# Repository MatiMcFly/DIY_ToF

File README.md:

# DIY ToF

Copyright (c) 2024-2025 Matthias Schär, Timon Burkard

This project is about creating a DIY (Do-It-Yourself) optical ToF (Time of Flight) distance measurement system.

It is a project work as part of the CAS (Certificate of Advanced Studies) in Sensors and Sensor Signal Conditioning, which is held at OST (Ostschweizer Fachhochschule) in Rapperswil CH.

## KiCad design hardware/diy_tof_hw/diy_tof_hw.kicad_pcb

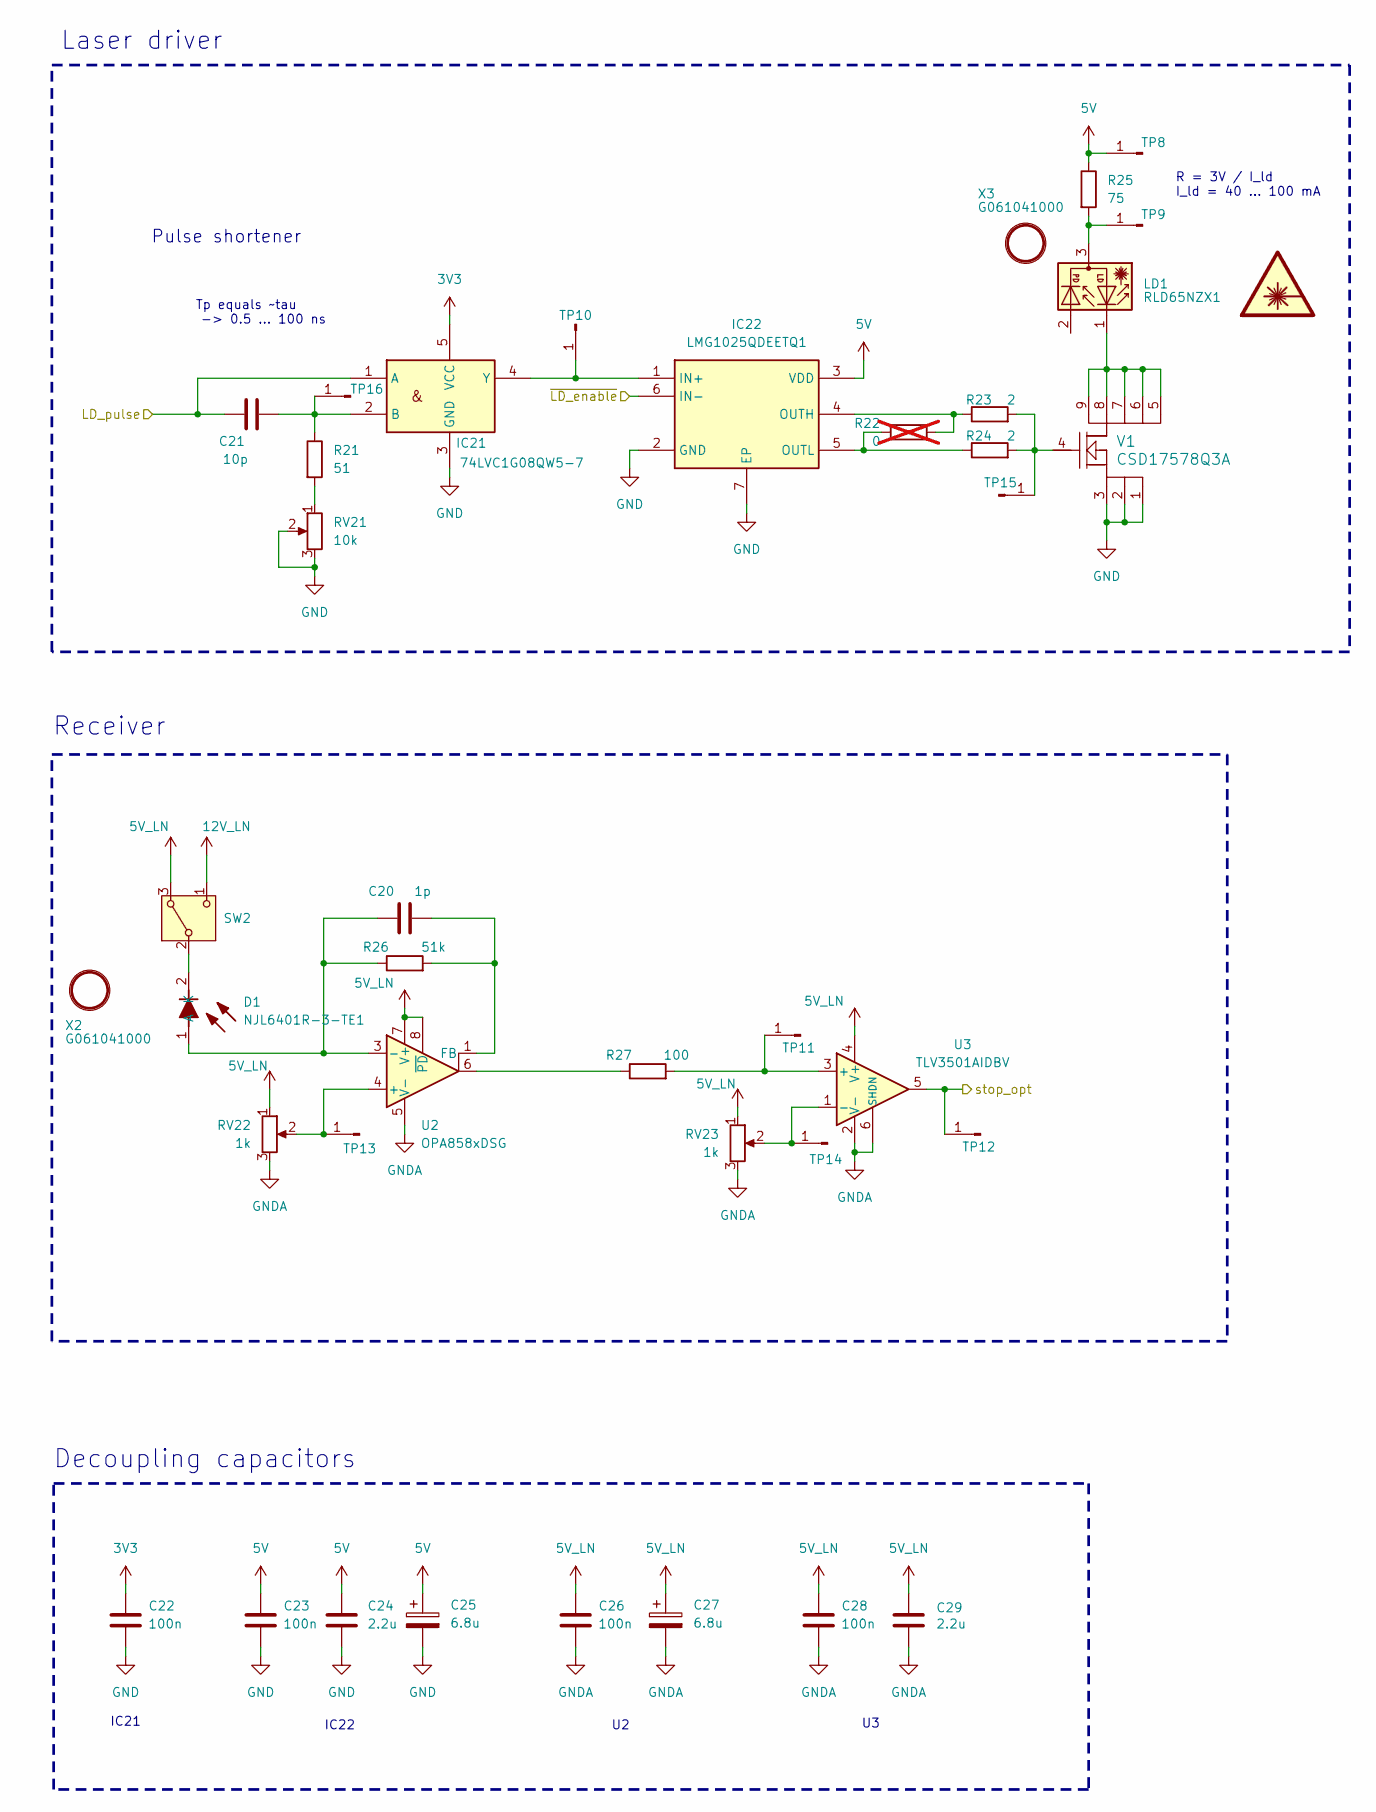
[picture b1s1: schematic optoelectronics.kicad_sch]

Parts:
C20: 1p; C_0402_1005Metric_Pad0.74x0.62mm_HandSolder
C21: 10p; C_0402_1005Metric_Pad0.74x0.62mm_HandSolder
C22, C23, C26, C28: 100n; C_0402_1005Metric_Pad0.74x0.62mm_HandSolder
C24, C29: 2.2u; C_0603_1608Metric_Pad1.08x0.95mm_HandSolder
C25, C27: 6.8u; CP_EIA-7343-43_Kemet-X_Pad2.25x2.55mm_HandSolder
D1: NJL6401R-3-TE1; NJL6401R3TE1; Mouser Part Number 513-NJL6401R-3-TE1
IC21: 74LVC1G08QW5-7; 74LVC1G08QW57; Mouser Part Number 621-74LVC1G08QW5-7
IC22: LMG1025QDEETQ1; SON65P200X200X80-7N; Mouser Part Number 595-LMG1025QDEETQ1
LD1: RLD65NZX1; RLD85PZJ400A
R21: 51; R_0402_1005Metric_Pad0.72x0.64mm_HandSolder
R22: 0; R_0402_1005Metric_Pad0.72x0.64mm_HandSolder; not fitted
R23, R24: 2; R_0402_1005Metric_Pad0.72x0.64mm_HandSolder
R25: 75; R_0603_1608Metric_Pad0.98x0.95mm_HandSolder
R26: 51k; R_0402_1005Metric_Pad0.72x0.64mm_HandSolder
R27: 100; R_0402_1005Metric_Pad0.72x0.64mm_HandSolder
RV21: 10k; Potentiometer_Bourns_3224W_Vertical
RV22, RV23: 1k; Potentiometer_Bourns_3224W_Vertical
SW2: SW_Nidec_CAS-120A1; Nidec_Copal_CAS-120A
TP8, TP9, TP10, TP11, TP12, TP13, TP14, TP15, TP16: Conn_01x01_Pin; PinHeader_1x01_P2.54mm_Vertical
U2: OPA858xDSG; WSON-8-1EP_2x2mm_P0.5mm_EP0.9x1.6mm
U3: TLV3501AIDBV; SOT-23-6
V1: CSD17578Q3A; DNH0008A
X2, X3: G061041000; Qioptiq_Mount

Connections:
3V3: C22.1, IC21.5 (VCC); also elsewhere on the board
5V: C23.1, C24.1, C25.1, IC22.3 (VDD), R25.1, TP8.1; also elsewhere on the board
5V_LN: C26.1, C27.1, C28.1, C29.1, RV22.1, RV23.1, SW2.3 (A), U2.7 (V+), U2.8 (~PD), U3.4 (V+); also elsewhere on the board
12V_LN: SW2.1 (C); also elsewhere on the board
/Optoelectronics/LD_pulse: C21.1, IC21.1 (A); also elsewhere on the board
/Optoelectronics/stop_opt: TP12.1, U3.5; also elsewhere on the board
/Optoelectronics/~LD_enable: IC22.6 (IN-); also elsewhere on the board
GND: C22.2, C23.2, C24.2, C25.2, IC21.3 (GND), IC22.2 (GND), IC22.7 (EP), RV21.2, RV21.3, V1.1, V1.2, V1.3; also elsewhere on the board
GNDA: C26.2, C27.2, C28.2, C29.2, RV22.3, RV23.3, U2.5 (V-), U2.9 (V-), U3.2 (V-), U3.6 (SHDN); also elsewhere on the board
unnamed: C20.1, D1.1 (A), R26.1, U2.3 (-)
unnamed: D1.2 (K), SW2.2 (B)
unnamed: C21.2, IC21.2 (B), R21.1, TP16.1
unnamed: IC21.4 (Y), IC22.1 (IN+), TP10.1
unnamed: IC22.4 (OUTH), R22.2, R23.1
unnamed: IC22.5 (OUTL), R22.1, R24.1
unnamed: LD1.1, V1.5, V1.6, V1.7, V1.8, V1.9
unnamed: R21.2, RV21.1
unnamed: R27.1, U2.6
unnamed: LD1.3, R25.2, TP9.1
unnamed: R27.2, TP11.1, U3.3 (+)
unnamed: RV22.2, TP13.1, U2.4 (+)
unnamed: RV23.2, TP14.1, U3.1 (-)
unnamed: R23.2, R24.2, TP15.1, V1.4
unnamed: C20.2, R26.2, U2.1 (FB)

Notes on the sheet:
Decoupling capacitors
IC22
Laser driver
R = 3V / I_ld I_ld = 40 ... 100 mA
Tp equals ~tau -> 0.5 ... 100 ns
IC21
Receiver
Pulse shortener

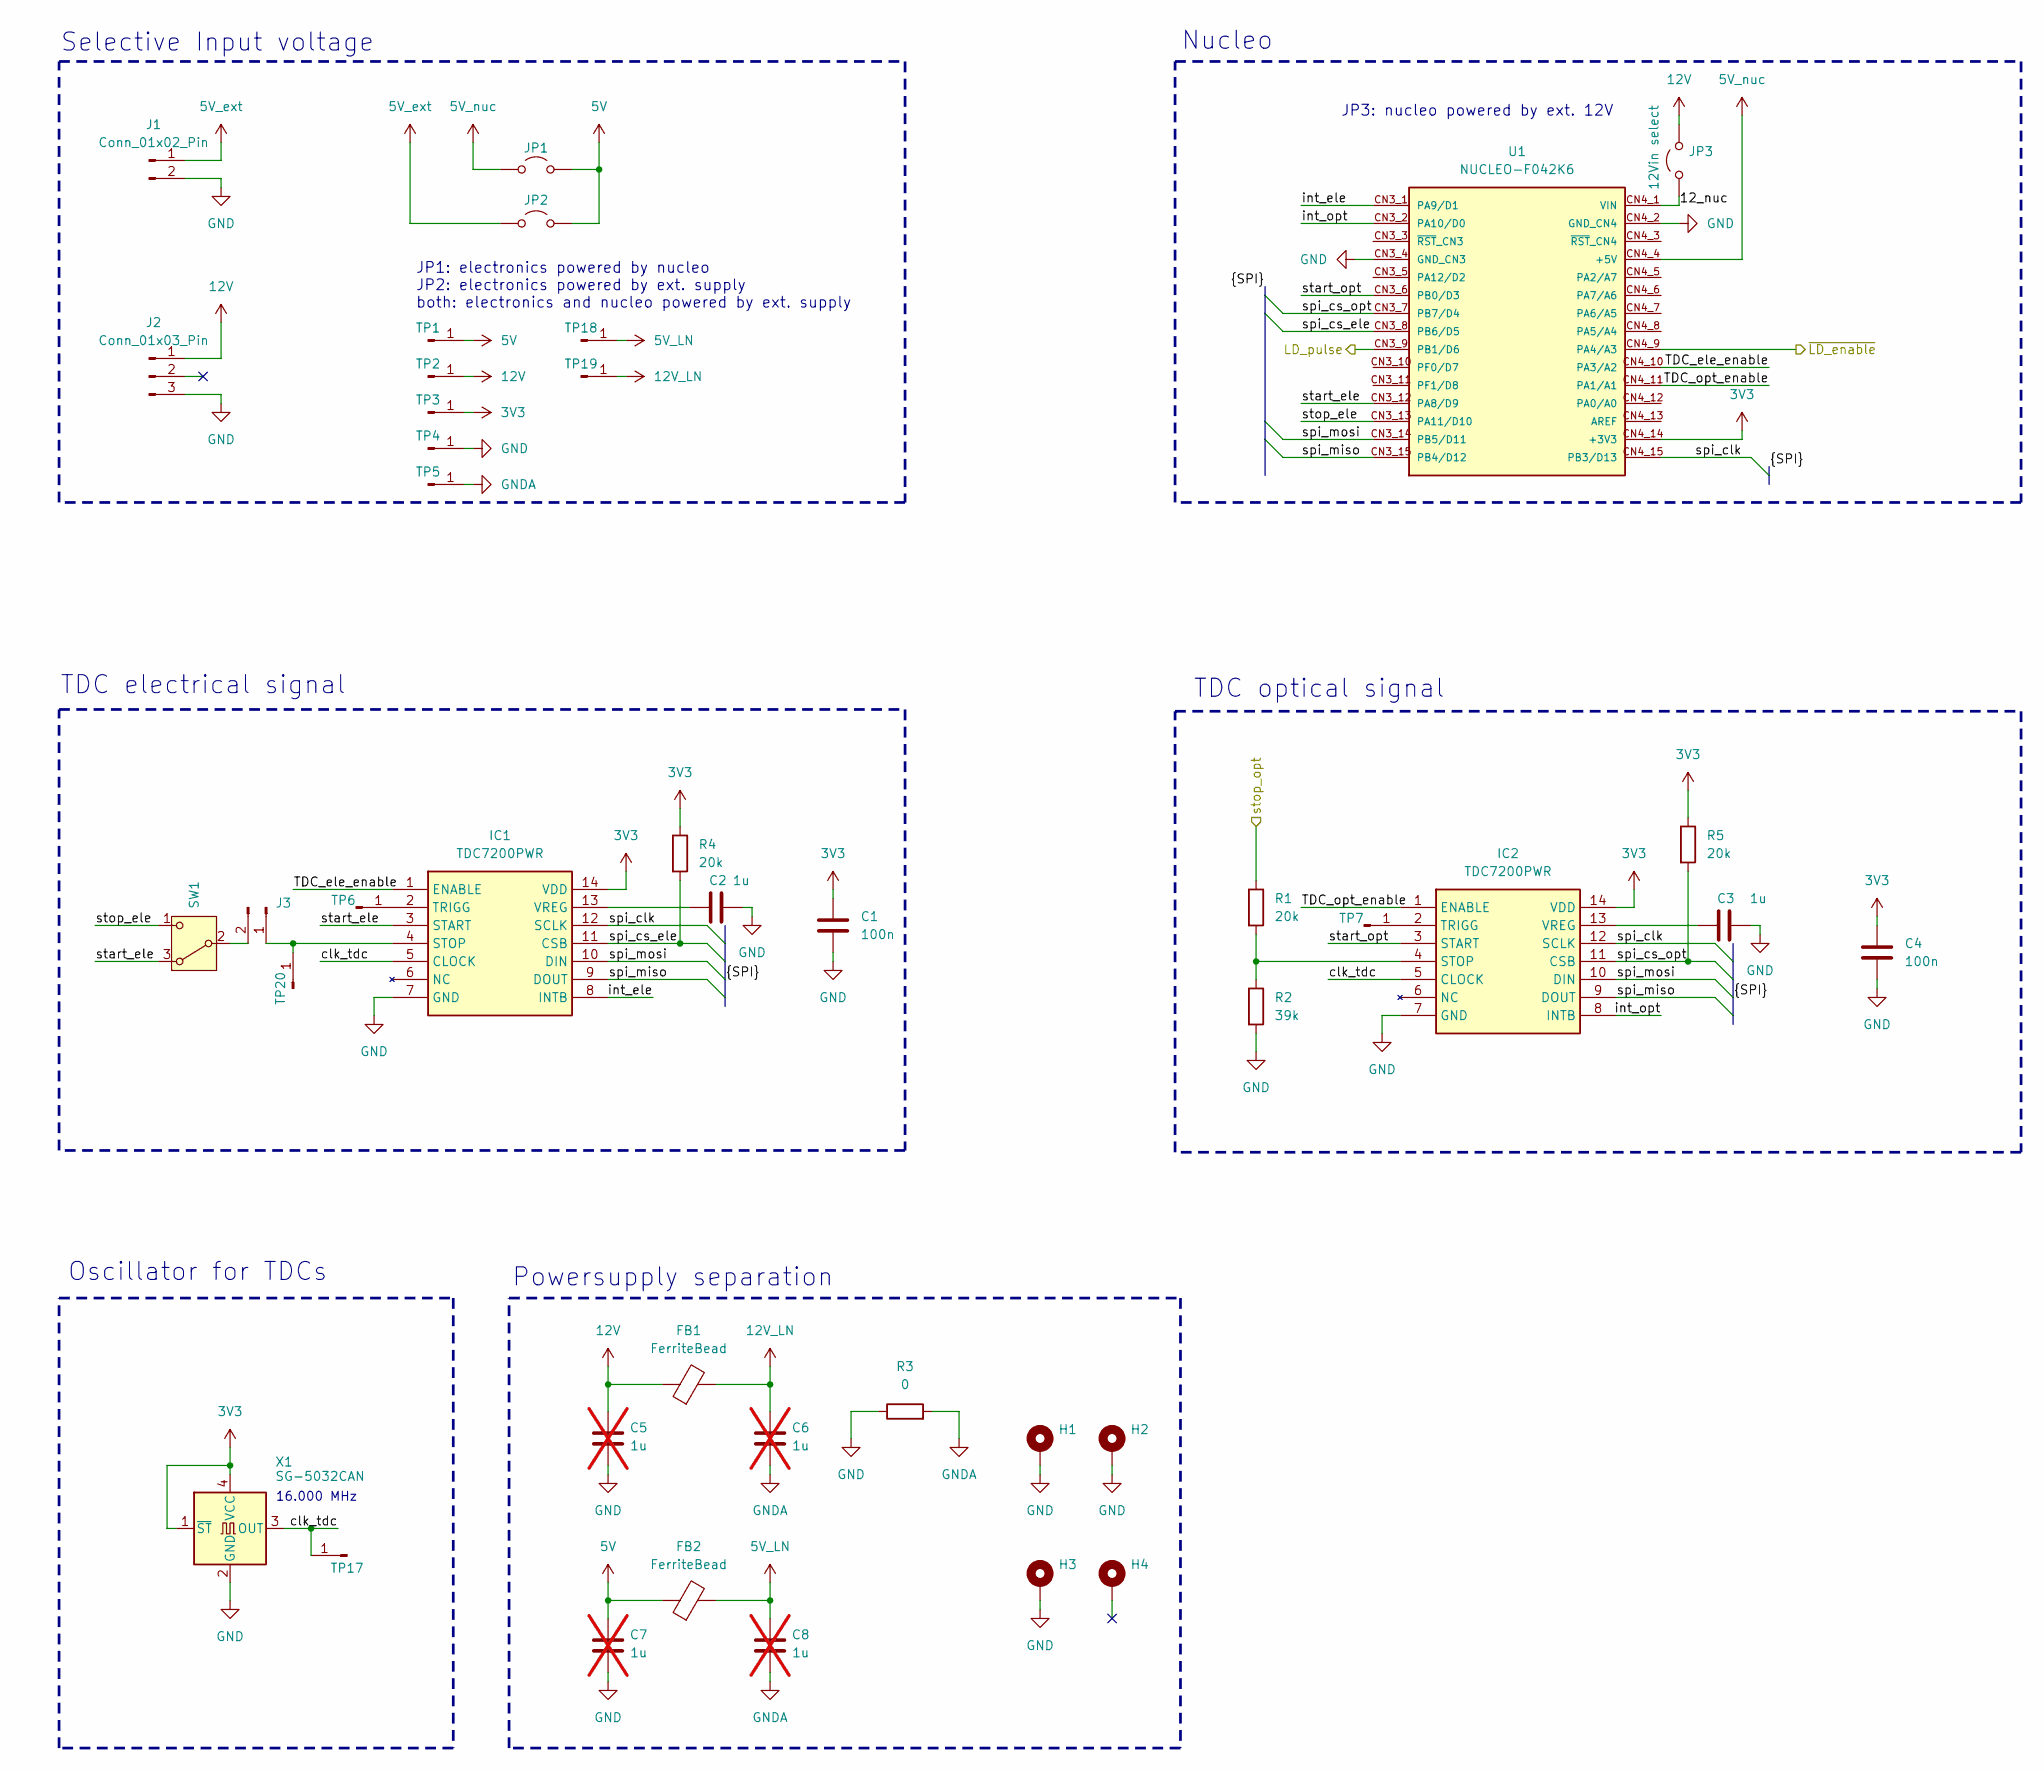
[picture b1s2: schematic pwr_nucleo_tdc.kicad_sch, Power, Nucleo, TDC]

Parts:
C1, C4: 100n; C_0402_1005Metric_Pad0.74x0.62mm_HandSolder
C2, C3: 1u; C_0402_1005Metric_Pad0.74x0.62mm_HandSolder
C5, C6, C7, C8: 1u; C_0402_1005Metric_Pad0.74x0.62mm_HandSolder; not fitted
FB1, FB2: FerriteBead; L_0402_1005Metric_Pad0.77x0.64mm_HandSolder
H1, H2, H3, H4: MountingHole_Pad; MountingHole_3.2mm_M3_DIN965_Pad_TopBottom
IC1, IC2: TDC7200PWR; SOP65P640X120-14N; Mouser Part Number 595-TDC7200PWR
J1, J3: Conn_01x02_Pin; Molex_KK-254_AE-6410-02A_1x02_P2.54mm_Vertical
J2: Conn_01x03_Pin; Molex_SL_171971-0003_1x03_P2.54mm_Vertical
JP1, JP2: Jumper_2_Open; TestPoint_2Pads_Pitch2.54mm_Drill0.8mm
JP3: 12Vin select; TestPoint_2Pads_Pitch2.54mm_Drill0.8mm
R1, R4, R5: 20k; R_0402_1005Metric_Pad0.72x0.64mm_HandSolder
R2: 39k; R_0402_1005Metric_Pad0.72x0.64mm_HandSolder
R3: 0; R_0402_1005Metric_Pad0.72x0.64mm_HandSolder
SW1: SW_Nidec_CAS-120A1; Nidec_Copal_CAS-120A
TP1, TP2, TP3, TP4, TP5, TP6, TP7, TP17, TP18, TP19, TP20: Conn_01x01_Pin; PinHeader_1x01_P2.54mm_Vertical
U1: NUCLEO-F042K6; MODULE_NUCLEO-F042K6; PARTREV 8
X1: SG-5032CAN; Oscillator_SMD_SeikoEpson_SG8002LB-4Pin_5.0x3.2mm_HandSolde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

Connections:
3V3: C1.1, C4.1, IC1.14 (VDD), IC2.14 (VDD), R4.1, R5.1, TP3.1, U1.CN4_14 (+3V3), X1.1 (~ST), X1.4 (VCC); also elsewhere on the board
5V: C7.2, FB2.1, JP1.2 (B), JP2.2 (B), TP1.1; also elsewhere on the board
5V_LN: C8.2, FB2.2, TP18.1; also elsewhere on the board
5V_ext: J1.1, JP2.1 (A)
5V_nuc: JP1.1 (A), U1.CN4_4 (+5V)
12V: C5.2, FB1.1, J2.1, JP3.2 (B), TP2.1
12V_LN: C6.2, FB1.2, TP19.1; also elsewhere on the board
/Optoelectronics/LD_pulse: U1.CN3_9 (PB1/D6); also elsewhere on the board
/Optoelectronics/stop_opt: R1.1; also elsewhere on the board
/Optoelectronics/~LD_enable: U1.CN4_9 (PA4/A3); also elsewhere on the board
/Power_Nucleo_TDC/12_nuc: JP3.1 (A), U1.CN4_1 (VIN)
/Power_Nucleo_TDC/TDC_ele_enable: IC1.1 (ENABLE), U1.CN4_10 (PA3/A2)
/Power_Nucleo_TDC/TDC_opt_enable: IC2.1 (ENABLE), U1.CN4_11 (PA1/A1)
/Power_Nucleo_TDC/clk_tdc: IC1.5 (CLOCK), IC2.5 (CLOCK), TP17.1, X1.3 (OUT)
/Power_Nucleo_TDC/int_ele: IC1.8 (INTB), U1.CN3_1 (PA9/D1)
/Power_Nucleo_TDC/int_opt: IC2.8 (INTB), U1.CN3_2 (PA10/D0)
/Power_Nucleo_TDC/spi_clk: IC1.12 (SCLK), IC2.12 (SCLK), U1.CN4_15 (PB3/D13)
/Power_Nucleo_TDC/spi_cs_ele: IC1.11 (CSB), R4.2, U1.CN3_8 (PB6/D5)
/Power_Nucleo_TDC/spi_cs_opt: IC2.11 (CSB), R5.2, U1.CN3_7 (PB7/D4)
/Power_Nucleo_TDC/spi_miso: IC1.9 (DOUT), IC2.9 (DOUT), U1.CN3_15 (PB4/D12)
/Power_Nucleo_TDC/spi_mosi: IC1.10 (DIN), IC2.10 (DIN), U1.CN3_14 (PB5/D11)
/Power_Nucleo_TDC/start_ele: IC1.3 (START), SW1.3 (A), U1.CN3_12 (PA8/D9)
/Power_Nucleo_TDC/start_opt: IC2.3 (START), U1.CN3_6 (PB0/D3)
/Power_Nucleo_TDC/stop_ele: SW1.1 (C), U1.CN3_13 (PA11/D10)
GND: C1.2, C2.2, C3.2, C4.2, C5.1, C7.1, H1.1, H2.1, H3.1, IC1.7 (GND), IC2.7 (GND), J1.2, J2.3, R2.2, R3.1, TP4.1, U1.CN3_4 (GND_CN3), U1.CN4_2 (GND_CN4), X1.2 (GND); also elsewhere on the board
GNDA: C6.1, C8.1, R3.2, TP5.1; also elsewhere on the board
unnamed: IC1.4 (STOP), J3.1, TP20.1
unnamed: IC1.2 (TRIGG), TP6.1
unnamed: C2.1, IC1.13 (VREG)
unnamed: IC2.4 (STOP), R1.2, R2.1
unnamed: IC2.2 (TRIGG), TP7.1
unnamed: C3.1, IC2.13 (VREG)
unnamed: J3.2, SW1.2 (B)

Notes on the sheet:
Powersupply separation
Oscillator for TDCs
Nucleo
JP1: electronics powered by nucleo JP2: electronics powered by ext. supply both: electronics and nucleo powered by ext. supply
TDC optical signal
Selective Input voltage
16.000 MHz
JP3: nucleo powered by ext. 12V
TDC electrical signal

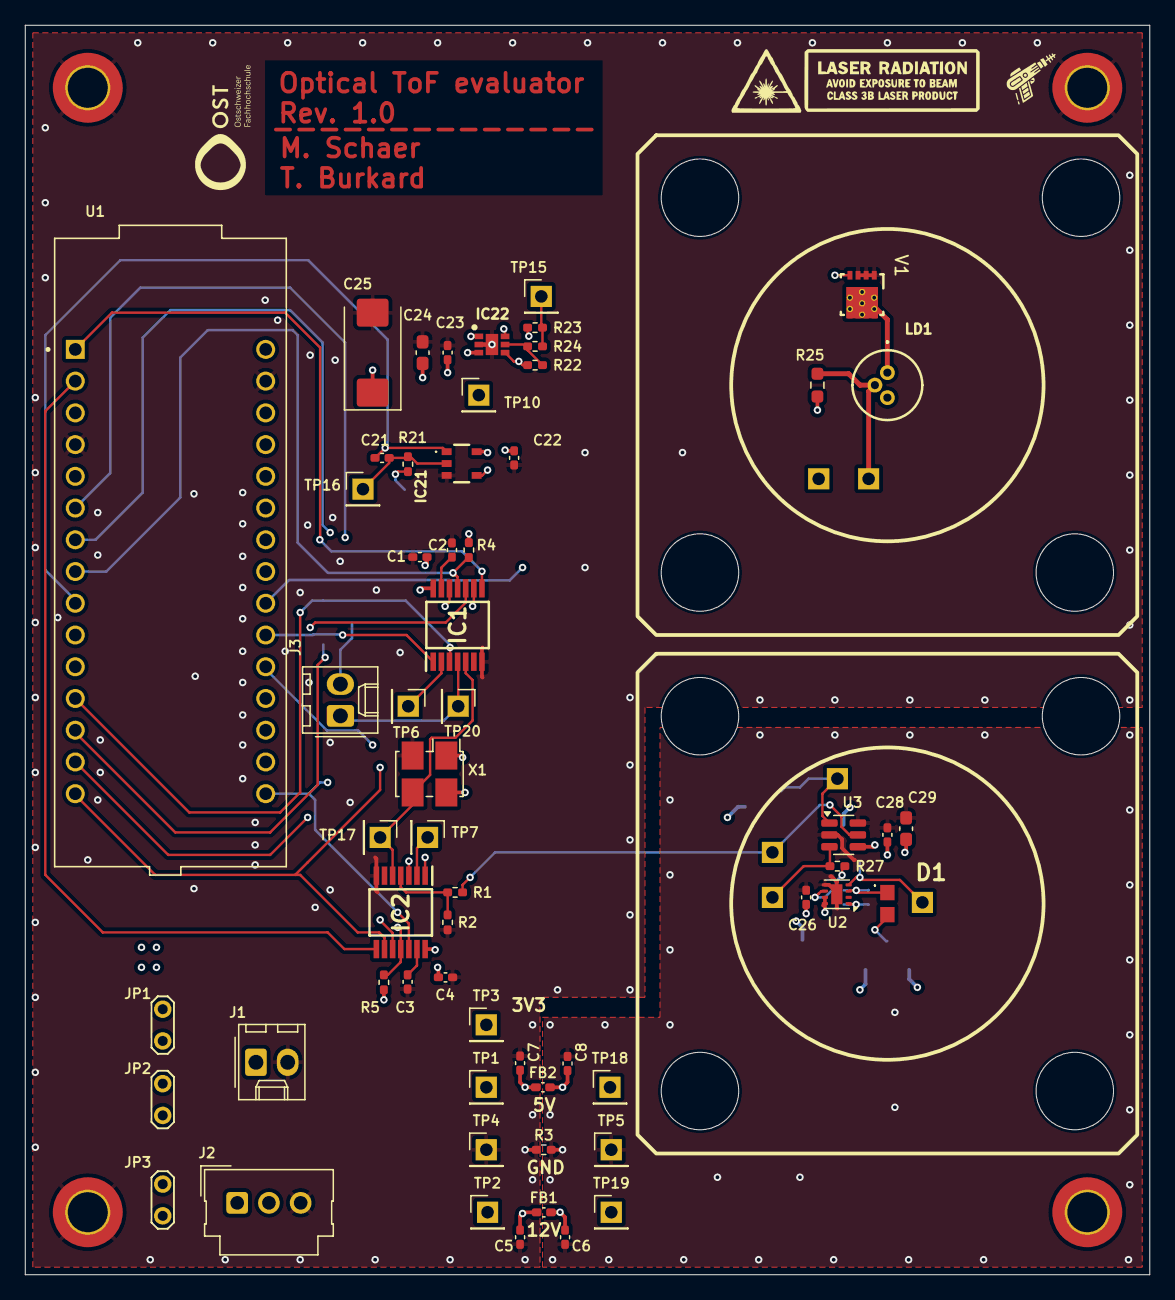
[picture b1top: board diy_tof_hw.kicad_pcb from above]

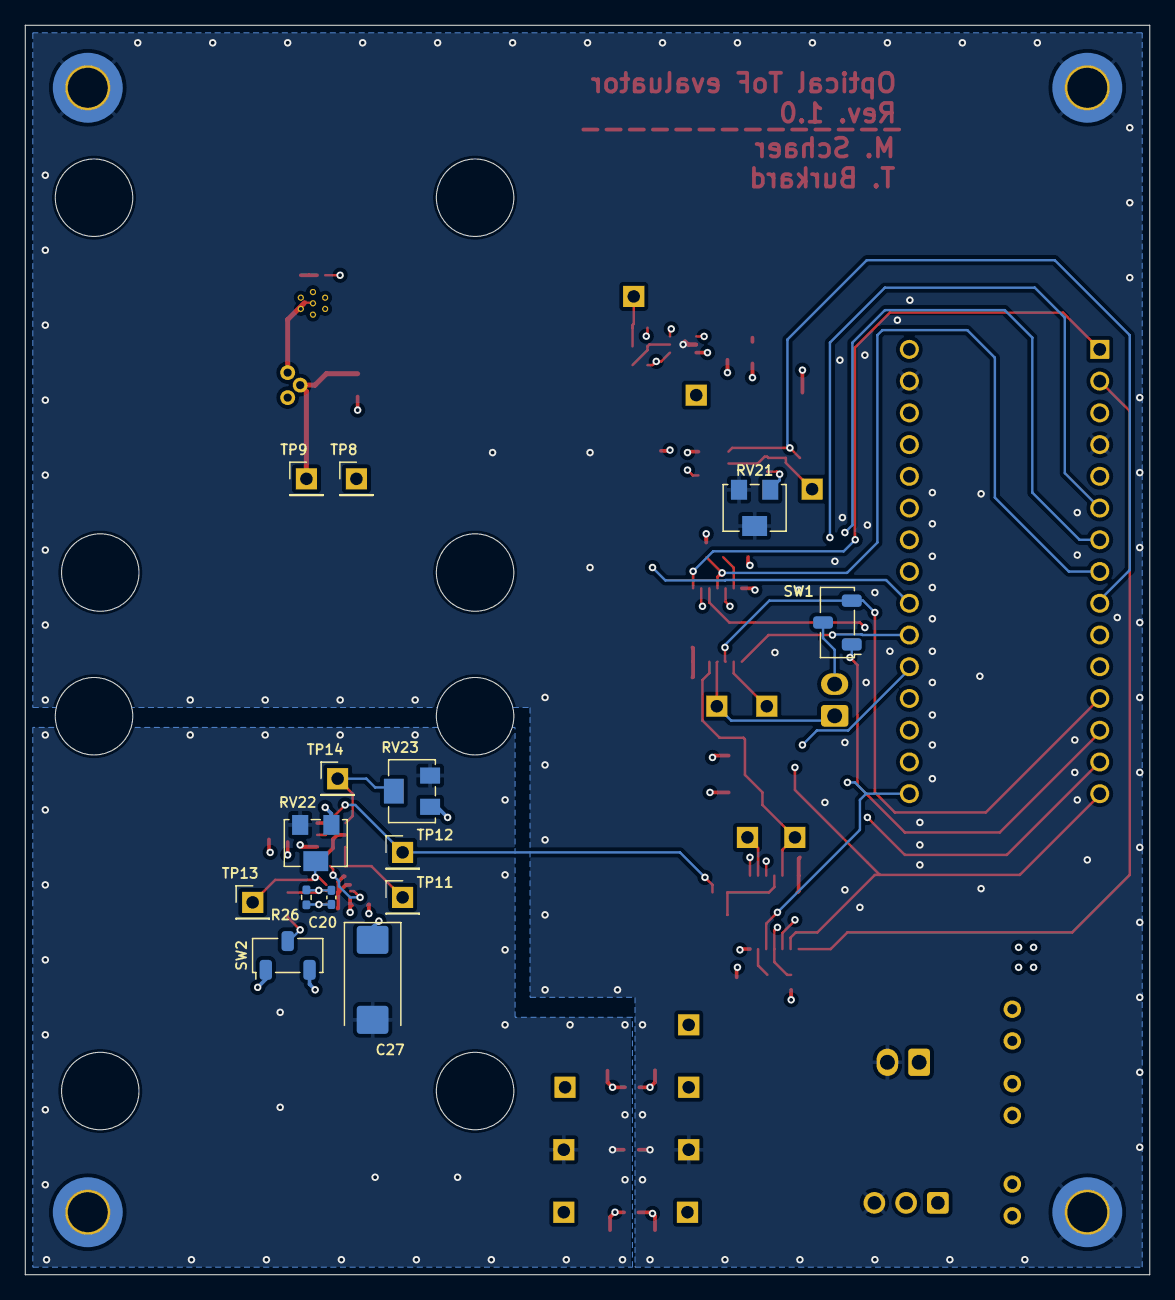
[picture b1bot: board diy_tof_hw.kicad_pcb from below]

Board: 4 copper layers, 90.0 x 100.0 mm, 80 parts (14 on the bottom side), 48 nets.

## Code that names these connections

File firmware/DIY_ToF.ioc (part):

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Mcu.Name=STM32F042K(4-6)Tx
Mcu.Package=LQFP32
Mcu.UserName=STM32F042K6Tx
PA1.GPIOParameters=GPIO_Label
PA1.GPIO_Label=TDC_OPT_ENABLE
PA1.Signal=GPIO_Output
PA10.GPIOParameters=GPIO_Label
PA10.GPIO_Label=INT_OPT
PA10.Signal=GPXTI10
PA11.GPIOParameters=GPIO_Label
PA11.GPIO_Label=STOP_ELE
PA11.Signal=S_TIM1_CH4
PA13.GPIOParameters=GPIO_Label
PA13.GPIO_Label=SWDIO
PA13.Mode=Serial_Wire
PA13.Signal=SYS_SWDIO
PA14.GPIOParameters=GPIO_Label
PA14.GPIO_Label=SWCLK
PA14.Mode=Serial_Wire
PA14.Signal=SYS_SWCLK
PA15.GPIOParameters=GPIO_Label
PA15.GPIO_Label=VCP_RX
PA15.Mode=Asynchronous
PA15.Signal=USART2_RX
PA2.GPIOParameters=GPIO_Label
PA2.GPIO_Label=VCP_TX
PA2.Mode=Asynchronous
PA2.Signal=USART2_TX
PA3.GPIOParameters=GPIO_Label
PA3.GPIO_Label=TDC_ELE_ENABLE
PA3.Signal=GPIO_Output
PA4.GPIOParameters=GPIO_Label
PA4.GPIO_Label=LD_ENABLE
PA4.Signal=GPIO_Output
PA8.GPIOParameters=GPIO_Label
PA8.GPIO_Label=START_ELE
PA8.Signal=S_TIM1_CH1
PA9.GPIOParameters=GPIO_Label
PA9.GPIO_Label=INT_ELE
PA9.Signal=GPXTI9
PB0.GPIOParameters=GPIO_Label
PB0.GPIO_Label=START_OPT
PB0.Signal=S_TIM3_CH3
PB1.GPIOParameters=GPIO_Label
PB1.GPIO_Label=LD_PULSE
PB1.Signal=S_TIM3_CH4
PB3.GPIOParameters=GPIO_Label
PB3.GPIO_Label=SPI_CLK
PB3.Mode=Full_Duplex_Master
PB3.Signal=SPI1_SCK
PB4.GPIOParameters=GPIO_Label
PB4.GPIO_Label=SPI_MISO
PB4.Mode=Full_Duplex_Master
PB4.Signal=SPI1_MISO
PB5.GPIOParameters=GPIO_Label
PB5.GPIO_Label=SPI_MOSI
PB5.Mode=Full_Duplex_Master
PB5.Signal=SPI1_MOSI
PB6.GPIOParameters=GPIO_Label
PB6.GPIO_Label=SPI_CS_ELE
PB6.Signal=GPIO_Output
PB7.GPIOParameters=GPIO_Label
PB7.GPIO_Label=SPI_CS_OPT
PB7.Signal=GPIO_Output
PF0-OSC_IN.GPIOParameters=GPIO_Label
PF0-OSC_IN.GPIO_Label=MCO
PF0-OSC_IN.Mode=HSE-External-Clock-Source
PF0-OSC_IN.Signal=RCC_OSC_IN
RCC.SYSCLKFreq_VALUE=48000000
RCC.SYSCLKSource=RCC_SYSCLKSOURCE_HSI48
board=NUCLEO-F042K6
boardIOC=true

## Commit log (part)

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2024-12-18 [general] initial commit
2024-12-18 [firmware] initial commit based on default MX board configuration
2024-12-18 [firmware] added GPIO configuration
    GPIO configuration for the following pins has been added:
    - SPI MISO
    - SPI MOSI
    - SPI CLK
    - SPI CS ELE
    - SPI CS OPT
2024-12-18 [docs] initial latex setup incl. some examples
2024-12-19 [hardware] initial commit containing KiCad project (schematics, layout and example library)
2024-12-20 [firmware/ci] trigger github action only for changes in firmware/ directory
    Github action only builds the STM32 FW project, no need to trigger it for changes in other directories.
2024-12-21 [hardware] added new templates for schematic files
2024-12-22 [hardware] drawn initial version of the power / nucleo sheet
2024-12-22 [firmware] modified IO signals - removed signal "PEAK_OPT" - added signals "LD_ENABLE", "LD_PULSE" and "TDC_ENABLE"
2024-12-22 [hardware] added schematics and library components for the laser driver as well as TIA circuit
2024-12-24 [hardware] cherry picked changes from review
    [hardware] add description text for JP3
    (cherry picked from commit 44d5712227eb7a57076d25d490ffb1ca2a138412)
    [hardware] use relative path for schematics template
    (cherry picked from commit 5e7c5f0f6d85de52cfba936180bf5f2080214473)
    [hardware] use explicit path to STEP files for U1, IC1, IC2, IC21, IC22
    (cherry picked from commit 2ea5c7e3506b8eddbb4935cb7e42b338c20b0635)
2024-12-24 [hardware, firmware] various review findings - added new signals TDC_opt/ele_enable - fixed placement and appearance of the optics mount - added switch for stop signal of the electrical TDC - replace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
2024-12-24 [hardware] renamed sheet "pwr_nucleo" to "pwr_nucleo_tdc"
2024-12-24 [hardware] added VCSEL, photodiode and some pcb graphics to the project
2024-12-24 [firmware] regenerated code due to previous IOC changes
    (cherry picked from commit fda93d0817f41cd3d09d576f384de487f9e32325)
2024-12-24 [hardware] updating 3D models again
2024-12-25 [hardware] added missing TP20
2024-12-25 [docs] initial chapter structure
2024-12-25 [hardware/minor] added title for optoelectronics schematic page
2024-12-25 [docs] remove examples from template
2024-12-25 [docs] added 3D views
2024-12-25 [docs] added 2nd professor
2024-12-25 [docs] added schematic drawings
2024-12-25 [docs] added calculations for photo current
2024-12-25 [docs] regenerated PDF due to latest changes
2024-12-26 [docs] move numbering of Formelverzeichnis a bit to the right
    To be harmonized with other Verzeichnisse
2024-12-26 [docs] added more references of components
2024-12-26 [docs] added some more text around calculations and schematics
2024-12-27 [hardware] changed footprint of R25 to 0603, updated some ICs footprint models in order to comply with e.g. via hole size constraints
2024-12-27 [hardware] initial version of the PCB layout
2024-12-27 [hardware] placed all components, some minor renaming (got rid of the "+" in front of all source-labels)
2024-12-27 [hardware] enlarged planes so that the PCB won't be produced with asymmetric copper planes - also added gerber output job
2024-12-27 [hardware] minor plane adjustments, removed a connection which is done via plane
2024-12-27 [hardware] review findings - moved powerplanes to layer In1 - added ground planes on all other layers - rerouting of signals around the nucleo board, leaving enough space for ground fills
2024-12-27 [docs] added PCB layout plots
2024-12-27 [docs] updated BOM based on recent changes in KiCAD
2024-12-27 [hardware/minor] add value for optic mountings
2025-01-08 [firmware/tdc] added initial version of TDC driver
2025-01-08 [firmware/tdc] added more register information
2025-01-08 [firmware/test] added quick example to test TDC driver implementation
2025-01-11 [firmware/tdc] add delay after CS high
    Just as an extra safety measure to ensure that we wait long enough
    after CS high until we start a measurement.
2025-01-11 [firmware/tdc] added `TDC_start()` and `TDC_read_result()` functions
2025-01-12 [utilities] added python script for stats calculation and plots
2025-01-12 [docs] added TDC driver and python script to Anhang
2025-01-12 [docs/minor] implemented max. line length of 120
    Not all editors support line wrapping. And this improves `git diff`.
2025-01-12 [utilities] added python script for stats calculation and plots for multiple measurements
2025-01-12 [docs] added python script multi to Anhang
2025-01-12 [docs] added chapter "Elektrische Messungen / Mode 1 vs. Mode 2"
2025-01-12 [docs] added chapter "Elektrische Messungen / Unterschiedliche Kabellängen"
2025-01-12 [docs] changed formulation about SW1 and J3 measurement settings
2025-01-15 [docs] added new section "konzept" since we need to explain various things like why we decided to use 2 TDCs; added some explanations for the nucleo schematics
2025-01-15 [docs] - added calculation for "lens gain" - added content to chapter "konzept" - added whole schematics to appendix - moved BoM to appendix - regenerated schematic with changes from v1.0
2025-01-15 [docs] added some more text to schematics
2025-01-15 [docs] rebuilt documentation.pdf after rebase and fixed another review finding
2025-01-15 [docs] no need to use sub-ps resolution
    THe TDC has 55~ps resolution. No need to use sub-ps resolution in docs.
2025-01-15 [docs] added chapter "Elektrische Messungen / Unterschiedliche Clock-Konfigurationen"
2025-01-15 [docs] applied feedback from review
2025-01-15 [docs/minor] harmonization of references to Anhang
    We agreed to call it `Anhang~\ref{...}` instead of `Anhang Kapitel~\ref{...}`
2025-01-15 [docs/minor] harmonization: all references to schematic designators should habe `\lstinline|...|`
2025-01-15 [docs] fixed typos
2025-01-15 [docs] added some more details about SW1
2025-01-15 [docs/minor] don't use `\acrshort{tdc}` as part of the component TDC7200
2025-01-15 [docs] restructuring: separate TEX files for each chapter
2025-01-16 [docs] added photos of demonstrator and lens
2025-01-16 [docs] added chapter "Simulationen / Laser Treiber"
2025-01-16 [docs] added chapter "Simulationen / Transimpedanzverstärker"
2025-01-16 [docs] structure: changed order of "Umsetzung" und "Simulationen"
    Makes more sense for "Simulationen" to come first. As we did the simulations
    first and only after we started the implementation (schematic, layout, ...)
2025-01-16 [docs] added some more equations for the optical path
2025-01-16 [docs] added text and a small diagram to the theory chapter
2025-01-16 [docs] added some basic text and a circuit diagram regarding the transimpedance amplifier
2025-01-17 [docs] review findings - some more correctures in various formulas - recalculated output power of the LD in both scenarios - better formulations + some typos fixed - better TIA schematics -> thanks T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
2025-01-17 [firmware] setup TIM1 channel 1 and 4 (start/stop ele) in order to do future measurements with less jitter
2025-01-17 [firmware] changed to 48 MHz clock by using HSI48 clock source
2025-01-17 [firmware] changed timer mode to one pulse mode - timer runs for 1.4ms, therefore the measurement loop delay was shortened to 2 ms
2025-01-17 [firmware] IO configuration for TIM3 in order to measure TDC optical the same way as the electrical one - start_opt and ld_pulse are now generated with TIM3
2025-01-18 [docs] rearrangements and picture updates - rearranged chapter "Umsetzung" into correct chronological order - applied the same changes to the appendix - moved all photos / 3D views / placement and la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
2025-01-18 [docs] sub sub chapters "Layout" and "3D View" - also modified text at beginning of chapter - added context for trimmers in the TIA schematics section
2025-01-18 [docs] recalculated optical power and light current more accurately, fixed a reference in the concept chapter - some formulations changed in the "Layout" sub sub chapter
2025-01-18 [docs] review findings
2025-01-18 [docs/minor] use real sine wave in dToF vs. iToF diagram
2025-01-18 [docs/minor] fixed typo
2025-01-18 [docs] added chapter "Messungen / Optische Messungen / Signalpfad Sender"
2025-01-18 [utilities] added python script for time plot with multiple log files
2025-01-18 [docs] added chapter "Messungen / Optische Messungen / ToF-Messungen via Spiegel"
2025-01-18 [docs] added chapter "Messungen / Optische Messungen / ToF-Messungen via Wand"
2025-01-18 [docs] added references for STM32CubeIDE and JLCPCB
2025-01-18 [docs] added more snippets about TDC FW driver
2025-01-19 [docs] added some more text to chapter "Messungen / Elektrische Messungen / Unterschiedliche Kabellängen"
2025-01-19 [docs] added chapter "Messungen / Elektrische Messungen / Unterschiedliche Kabellängen mit DSO"
2025-01-19 [docs] added time plot of TDC results to "Unterschiedliche Kabellängen mit DSO"
2025-01-19 [utilities] updated python script for multiple ToF values to handle different dataset sizes
    Sometimes we don't have the exact same number of ToF values per column, python
    script shouldn't go crazy in this case.
2025-01-19 [docs] labeled new dso plots for different cable length measurements
2025-01-19 [docs/minor] harmonized time plots to be in the same unit
    Time plots always in ps with 1000th separator.
2025-01-19 [docs] README: added picture
2025-01-19 [docs] added content to chapter "Fazit"
2025-01-19 [docs] added diameter values of copper wire used for electrical measurements
2025-01-19 [docs] added note about clusters in optical measurements
2025-01-19 [docs/minor] removed TODO comments which are not needed anymore
2025-01-19 [docs] update README
2025-01-20 [docs] uploaded fixed space vector graphics file for a measurement since it broke the LaTeX build
2025-01-20 [docs] proofreading subchapter "Theorie"
2025-01-20 [docs] added introductory subsection, labeled all sections
2025-01-20 [docs] added corrections to chapter "Umsetzung"
2025-01-20 [docs] regenerated pdfs due to recent changes
2025-01-20 [docs] moved documentation into subdirectory to make space for upcoming presentation
2025-01-20 [docs/presentation] initial commit based on template
2025-01-20 [docs/presentation] settings: apply correct style for \codehighlight
2025-01-20 [docs/presentation] settings: added \mytable command
2025-01-20 [docs/documentation] adjusted paths due to change in folder structure
2025-01-20 [docs/presentation] added inital structure and inserted some figures
2025-01-20 [docs/documentation] added abstract
2025-01-20 [docs] added blockdiagram
2025-01-20 [docs/presentation] Makefile: add dependency for diagrams from documentation/
2025-01-20 [docs] regenerated PDFs due to latest changes
2025-01-21 [docs/documentation] titlepage: removed legal notice
    No need to have a legal note acc. to Prof. Kehl. Also doesn't make a lot of
    sense as we have it in a public repo on GitHub ;)
2025-01-22 [docs/documentation] applied feedback from proofreading of Katrin
2025-01-22 [docs/documentation] Einleitung: added chapter names
2025-01-22 [docs/documentation] renamed chapter "Messungen" to "Resultate"
    More common and professional to call it "Resultate".
2025-01-22 [docs/documentation] applied feedback from review
2025-01-23 [docs/presentation] changed DSO plots
2025-01-23 [docs/presentation] added icons for electrical vs. optical parts
    Make it easier for the audience to follow the presentation by visual differentiation
    between eletrical and optical parts.
2025-01-23 [docs/presentation] regenerated PDF due to latest changes
2025-01-23 [utilities] added python script which live plots ToF values
    This will be used for the demonstration part of the presentation.
2025-01-23 [utilities] added requirements.txt
2025-01-23 [presentation] added text to chapter "ziele"
2025-01-23 [presentation] regenerated pdf due to recent changes
2025-01-23 [docs/presentation] removed "Quellen"
    We don't need it, all assets are from us.
2025-01-23 [docs/presentation] minor rewording
2025-01-24 [general] updated README
    Due to change in docs/ directory structure the link to the cover picture was broken
2025-03-19 [docs/documentation] added English version
    Translation was done by DeepL.
2025-03-24 [docs] translated some diagrams to English
    Lets follow the same convention for all diagrams: They are in English.
2025-03-25 TBCP
2025-03-27 [docs/presentation] translated to English by DeepL
